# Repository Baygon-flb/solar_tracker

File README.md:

# solar_tracker
## Seguidor solar

Este projeto implementa um experimento de um seguidor que localiza uma fonte de luz e
mantém um sensor RGB apontado perpendicularmente para esta fonte, utilizando um arduíno Nano
como controlador. 

O objetivo é fazer a medição das intensidades dos componentes expectrais cromáticos RGB da luz 
solar ao longo de um dia, a partir do que é possível também calcular a temperatura de cor e a
intensidade total. 

Para essa medição é utilizado um módulo TCS34725 RGB Light Sensor.

O projeto conta com dois servos motores, um que controla a coordenada de altura e outro a 
coordenada de azimute do sensor, além de 4 LDR's, dispostos nas extremidades da placa de 
suporte do sensor, posicionados nos quadrantes presumidos como os pontos cardeais N,S,L e O. 

Com base na diferença de leitura dos LDR's, os motores são acionados, reposicionando a placa de
suporte do sensor, objetivando reorientar o conjunto até que haja convergência nos valores lidos 
dos LDR's (todos recebendo a mesma quantidade de luz), dentro de uma margem de erro estipulada, 
garantindo assim que o sensor estará, o máximo possível, apontado de forma perpendicular à fonte 
de luz. 

A leitura dos dados do sensor é realizada em um intervalo definido de tempo. Essas leituras são 
armazenadas na memória EEprom do arduíno e depois baixadas, via conexão serial, para um terminal, 
afim de que possam ser então capturados e tratados. Para controlar o intervalo de coleta dos 
dados do sensor é utilizado um módulo RTC (DS1307).

Os servos são controlados (sem uso de bilbioteca) através de uma rotina de timer interrupt, afim 
de garantir que não ocorrerão flickers ou jammers que comprometam a estabilidade da posição do 
sensor.

O detalhamento completo da elaboração e construção do projeto pode ser encontrado na pasta de 
documentação (pasta DOC).

Os componentes utilizados no projeto são:

* Arduino nano V3
* Módulo sensor TCS34725
* Módulo RTC DS1307
* Módulo StepDown DC/DC LM2596

As pastas do projeto são:
* CAD - Desenhos DWG dos componentes de montagem da caixa e suportes
* KICAD - Esquemático eletrônico e PCB
* INO - Arquivos de Sketch para a IDE do arduino
* STL - Arquivos para impressão das partes dos componentes de montagem
* DOC - Documentação do projeto

@baygon-flb

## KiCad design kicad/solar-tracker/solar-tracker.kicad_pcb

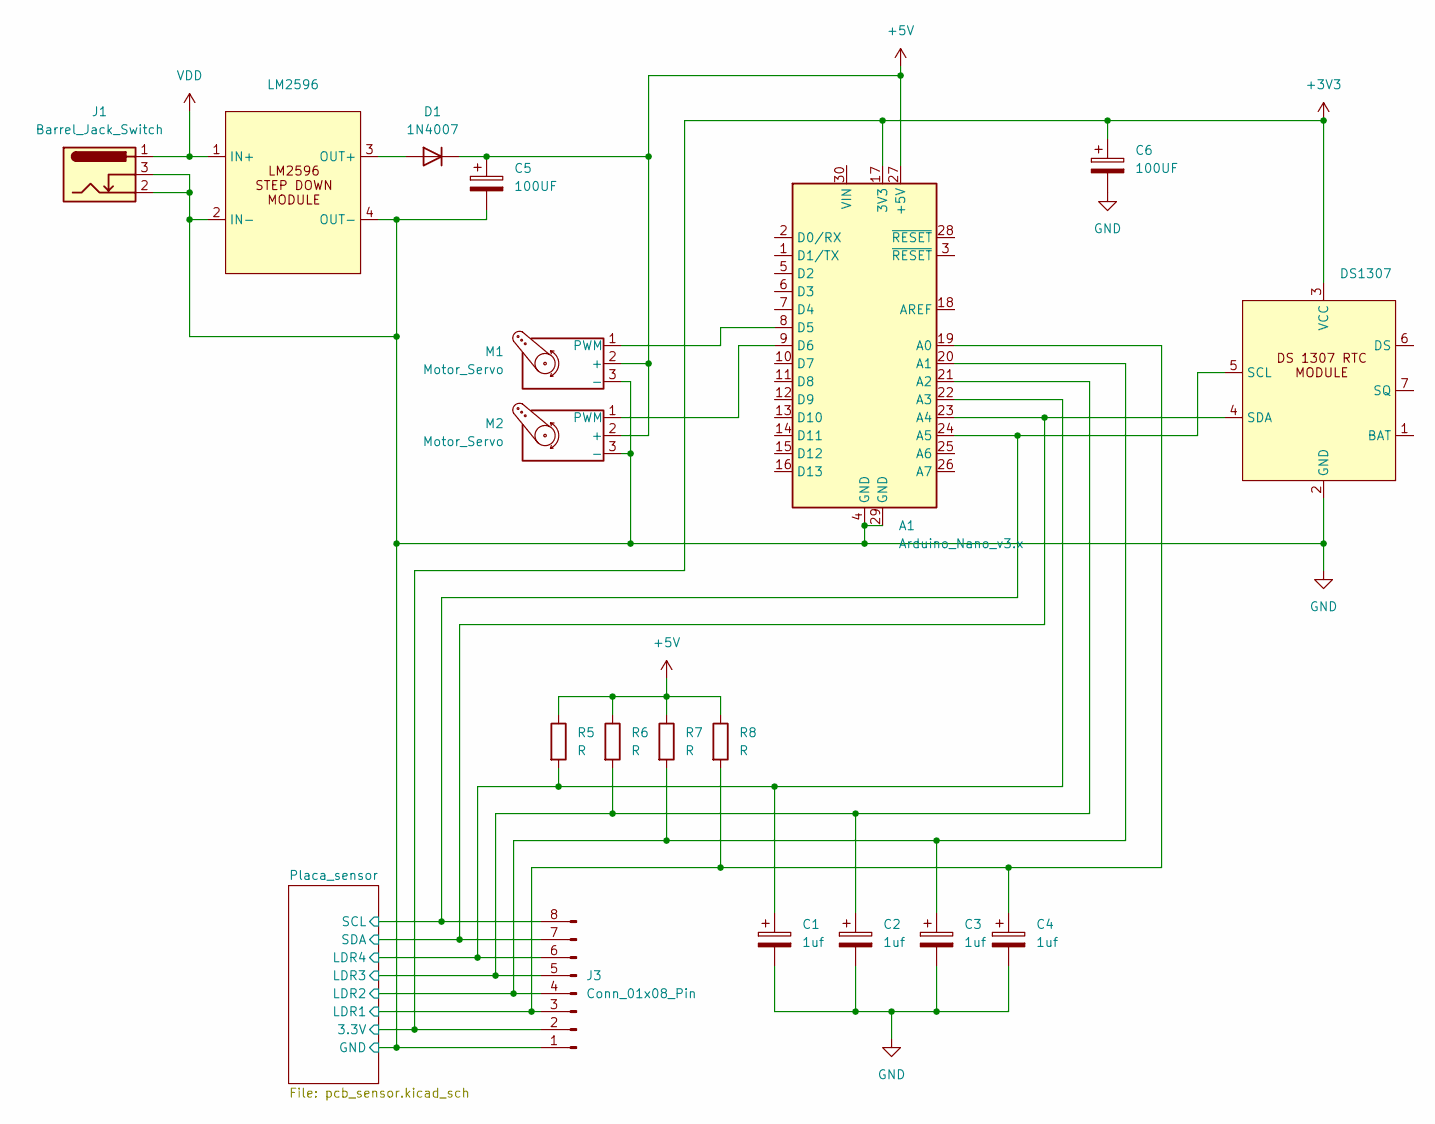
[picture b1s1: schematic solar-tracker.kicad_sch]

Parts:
A1: Arduino_Nano_v3.x; Arduino_Nano
C1, C2, C3, C4: 1uf; CP_Radial_D6.3mm_P2.50mm
C5, C6: 100UF; CP_Radial_D6.3mm_P2.50mm
D1: 1N4007; D_DO-41_SOD81_P10.16mm_Horizontal
DS1307: DS1307_RTC_MODULE
J1: Barrel_Jack_Switch; BarrelJack_Horizontal
J3: Conn_01x08_Pin; PinHeader_1x08_P2.54mm_Vertical_large_pad
LM2596: LM2596_Step_Down_module
M1, M2: Motor_Servo; PinHeader_1x03_P2.54mm_Vertical
R5, R6, R7, R8: R; resistor_250mw_12mm

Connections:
+3V3: A1.17 (3V3), C6.1, DS1307.3 (VCC), J3.2; also elsewhere on the board
+5V: A1.27 (+5V), C5.1, D1.1 (K), M1.2 (+), M2.2 (+), R5.1, R6.1, R7.1, R8.1
/Placa_sensor/LDR1: A1.19 (A0), C4.1, J3.3, R8.2; also elsewhere on the board
/Placa_sensor/LDR2: A1.20 (A1), C3.1, J3.4, R7.2; also elsewhere on the board
/Placa_sensor/LDR3: A1.21 (A2), C2.1, J3.5, R6.2; also elsewhere on the board
/Placa_sensor/LDR4: A1.22 (A3), C1.1, J3.6, R5.2; also elsewhere on the board
/Placa_sensor/SCL: A1.24 (A5), DS1307.5 (SCL), J3.8; also elsewhere on the board
/Placa_sensor/SDA: A1.23 (A4), DS1307.4 (SDA), J3.7; also elsewhere on the board
GND: A1.4 (GND), A1.29 (GND), C1.2, C2.2, C3.2, C4.2, C5.2, C6.2, DS1307.2 (GND), J1.2, J1.3, J3.1, LM2596.2 (IN-), LM2596.4 (OUT-), M1.3 (-), M2.3 (-); also elsewhere on the board
unnamed: A1.8 (D5), M1.1 (PWM)
unnamed: A1.9 (D6), M2.1 (PWM)
unnamed: D1.2 (A), LM2596.3 (OUT+)
VDD: J1.1, LM2596.1 (IN+)

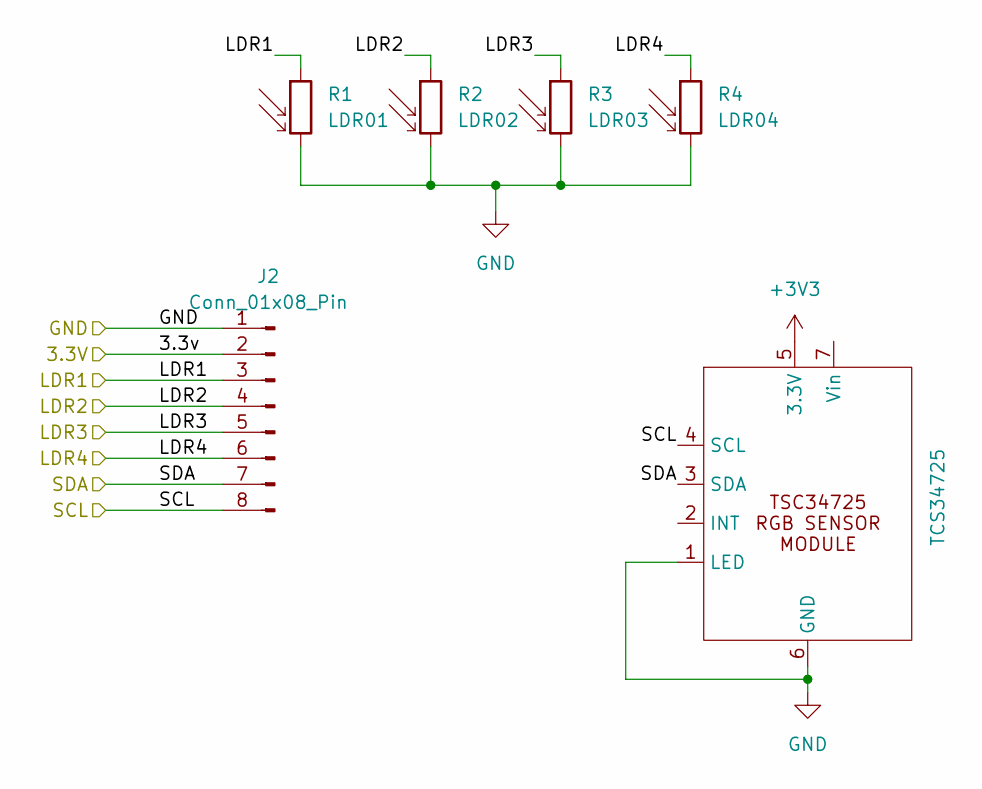
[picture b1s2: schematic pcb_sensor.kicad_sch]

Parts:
J2: Conn_01x08_Pin; PinHeader_1x08_P2.54mm_Vertical_large_pad
R1: LDR01; R_LDR_5.1x4.3mm_P3.4mm_Vertical
R2: LDR02; R_LDR_5.1x4.3mm_P3.4mm_Vertical
R3: LDR03; R_LDR_5.1x4.3mm_P3.4mm_Vertical
R4: LDR04; R_LDR_5.1x4.3mm_P3.4mm_Vertical
TCS34725: TSC34725_RGB_SENSOR

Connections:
+3V3: J2.2, TCS34725.5 (3.3V); also elsewhere on the board
/Placa_sensor/LDR1: J2.3, R1.1; also elsewhere on the board
/Placa_sensor/LDR2: J2.4, R2.1; also elsewhere on the board
/Placa_sensor/LDR3: J2.5, R3.1; also elsewhere on the board
/Placa_sensor/LDR4: J2.6, R4.1; also elsewhere on the board
/Placa_sensor/SCL: J2.8, TCS34725.4 (SCL); also elsewhere on the board
/Placa_sensor/SDA: J2.7, TCS34725.3 (SDA); also elsewhere on the board
GND: J2.1, R1.2, R2.2, R3.2, R4.2, TCS34725.1 (LED), TCS34725.6 (GND); also elsewhere on the board

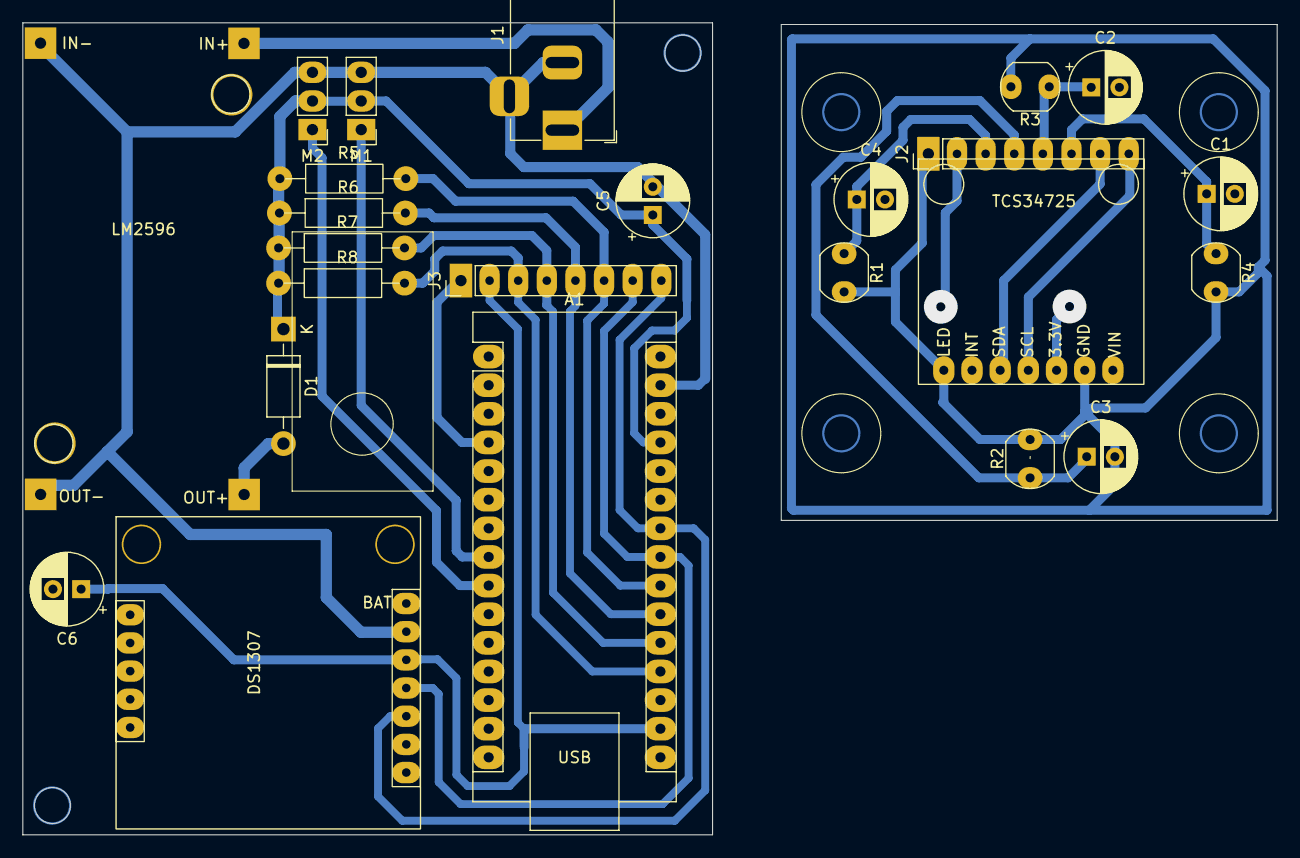
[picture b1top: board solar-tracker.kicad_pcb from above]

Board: 2 copper layers, 111.3 x 72.0 mm, 24 parts (0 on the bottom side), 13 nets.

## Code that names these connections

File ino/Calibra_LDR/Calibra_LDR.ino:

//Calibra_LDR

#define PIN_N A0 //LDR1 leste 
#define PIN_O A1 //LDR2 Norte
#define PIN_L A2 //LDR3 Sul
#define PIN_S A3 //LDR4 oeste
#define SERIAL_RATE 115200

long tempo = 0;

void setup() {
  Serial.begin( SERIAL_RATE );
  // Configurando os LDRS
  pinMode( PIN_L, INPUT_PULLUP );    
  pinMode( PIN_N, INPUT_PULLUP );
  pinMode( PIN_S, INPUT_PULLUP );
  pinMode( PIN_O, INPUT_PULLUP );

  Serial.println(F("---------------"));
  Serial.println("offset dos LDR's");
  Serial.println( " N     S     L     O ");

}

void loop() {
  if ( abs( millis()-tempo) > 1000 ) { 
    float L=0, N=0, S=0, O=0;
    for ( int i=1; i<10; i++ ) {
      L += analogRead( PIN_L );
      N += analogRead( PIN_N );
      S += analogRead( PIN_S );
      O += analogRead( PIN_O );
    }
    L = L/10;
    N = N/10;
    S = S/10;
    O = O/10;

    float offset_N = (( S - N )/2)/N;
    float offset_S = (( N - S )/2)/S;
    float offset_L = (( O - L )/2)/L;
    float offset_O = (( L - O )/2)/O;
    
    Serial.print( offset_N );
    Serial.print("  ");
    Serial.print( offset_S );
    Serial.print("  ");
    Serial.print( offset_L );
    Serial.print("  ");
    Serial.println( offset_O );

    tempo = millis();
  }
  delay(100);
}

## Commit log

2025-06-04 kicad
2025-06-05 PCB_sensor
